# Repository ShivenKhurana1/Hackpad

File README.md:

# Macropad v1

## Features
- 6 Switches
- 1 Rotary knob 
- 4 LEDs
- 1 OLED 32x128

## Specifications
BOM:
- 6x Cherry MX Switches
- 7x Blank DSA 1.00u keycaps
- 4x SK6812 MINI E Neopixels
- 1x EC11 Rotary Encoder - RotaryEncoder_Switch
- 1x Rotary knob
- 1x XIAO RP2040
- 6x M3x5mx4mm heatset insert
- 6x M3x16mm screws

## Firmware Overview  

The firmware of this macropad was made using KMK.

### Schematics

### PCB

### Case
[Onshape](https://cad.onshape.com/documents/5906443835429a70686708c9/w/0a37427c6684fd944ae1fb2e/e/fe81ea7ceb2d4edde9dfcf52)

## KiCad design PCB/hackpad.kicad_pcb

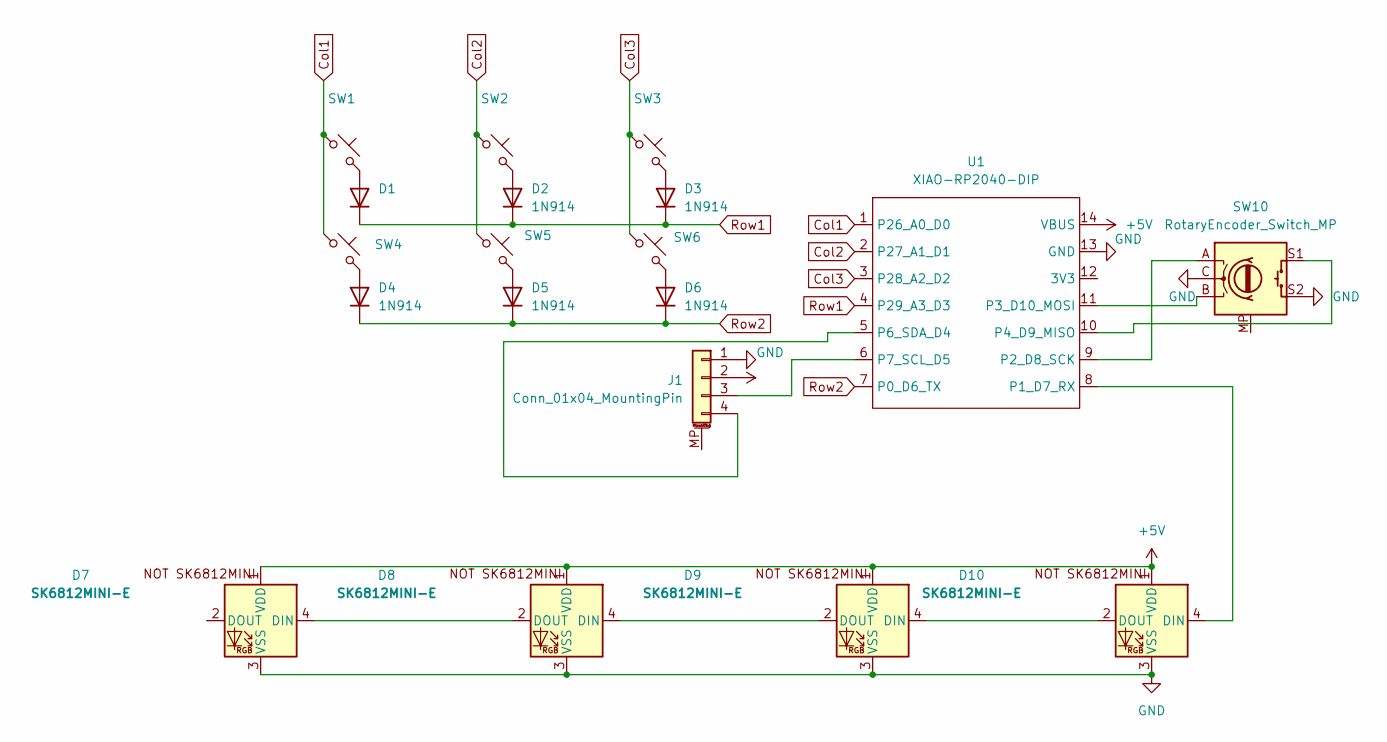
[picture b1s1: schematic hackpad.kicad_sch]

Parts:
D1, D2, D3, D4, D5, D6: 1N914; D_DO-35_SOD27_P7.62mm_Horizontal
D7, D8, D9, D10: SK6812MINI-E; SK6812MINI-E_fixed
J1: Conn_01x04_MountingPin; PinHeader_1x04_P2.54mm_Vertical
SW1, SW2, SW3, SW4, SW5, SW6: SW_Push_45deg; SW_Cherry_MX_1.00u_PCB
SW10: RotaryEncoder_Switch_MP; RotaryEncoder_Alps_EC11E-Switch_Vertical_H20mm
U1: XIAO-RP2040-DIP

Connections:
+5V: D7.1 (VDD), D8.1 (VDD), D9.1 (VDD), D10.1 (VDD), J1.2, U1.14 (VBUS)
Col1: SW1.1, SW4.1, U1.1 (P26_A0_D0)
Col2: SW2.1, SW5.1, U1.2 (P27_A1_D1)
Col3: SW3.1, SW6.1, U1.3 (P28_A2_D2)
GND: D7.3 (VSS), D8.3 (VSS), D9.3 (VSS), D10.3 (VSS), J1.1, SW10.C, SW10.S2, U1.13 (GND)
unnamed: D1.2 (A), SW1.2
unnamed: D2.2 (A), SW2.2
unnamed: D3.2 (A), SW3.2
unnamed: D4.2 (A), SW4.2
unnamed: D5.2 (A), SW5.2
unnamed: D6.2 (A), SW6.2
unnamed: D7.4 (DIN), D8.2 (DOUT)
unnamed: D8.4 (DIN), D9.2 (DOUT)
unnamed: D10.4 (DIN), U1.8 (P1_D7_RX)
unnamed: D9.4 (DIN), D10.2 (DOUT)
unnamed: J1.3, U1.6 (P7_SCL_D5)
unnamed: J1.4, U1.5 (P6_SDA_D4)
unnamed: SW10.A, U1.9 (P2_D8_SCK)
unnamed: SW10.B, U1.11 (P3_D10_MOSI)
unnamed: SW10.S1, U1.10 (P4_D9_MISO)
Row1: D1.1 (K), D2.1 (K), D3.1 (K), U1.4 (P29_A3_D3)
Row2: D4.1 (K), D5.1 (K), D6.1 (K), U1.7 (P0_D6_TX)

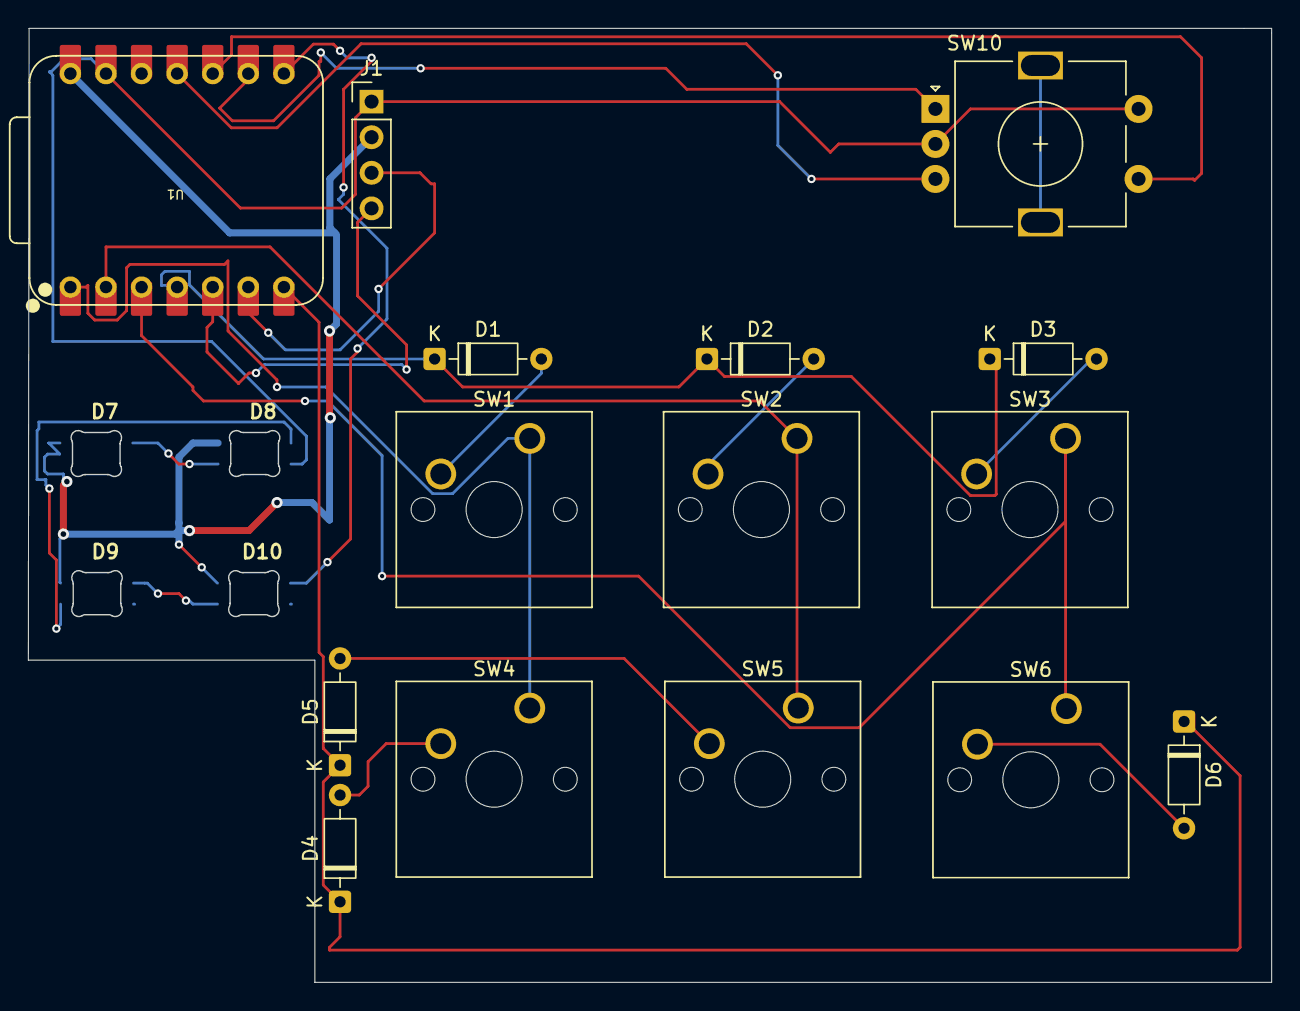
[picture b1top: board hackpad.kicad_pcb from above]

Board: 2 copper layers, 88.8 x 68.1 mm, 19 parts (0 on the bottom side), 22 nets.

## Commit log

2026-03-02 init
2026-03-02 assets
2026-03-02 Add README for Macropad v1 with features and specs
2026-03-02 Increase image sizes in README.md
2026-03-04 Fix image tag for CAD in README
2026-03-04 Fix CAD image source in README
    Updated image source for CAD in the README.
2026-03-05 Add Onshape link to the Case section
